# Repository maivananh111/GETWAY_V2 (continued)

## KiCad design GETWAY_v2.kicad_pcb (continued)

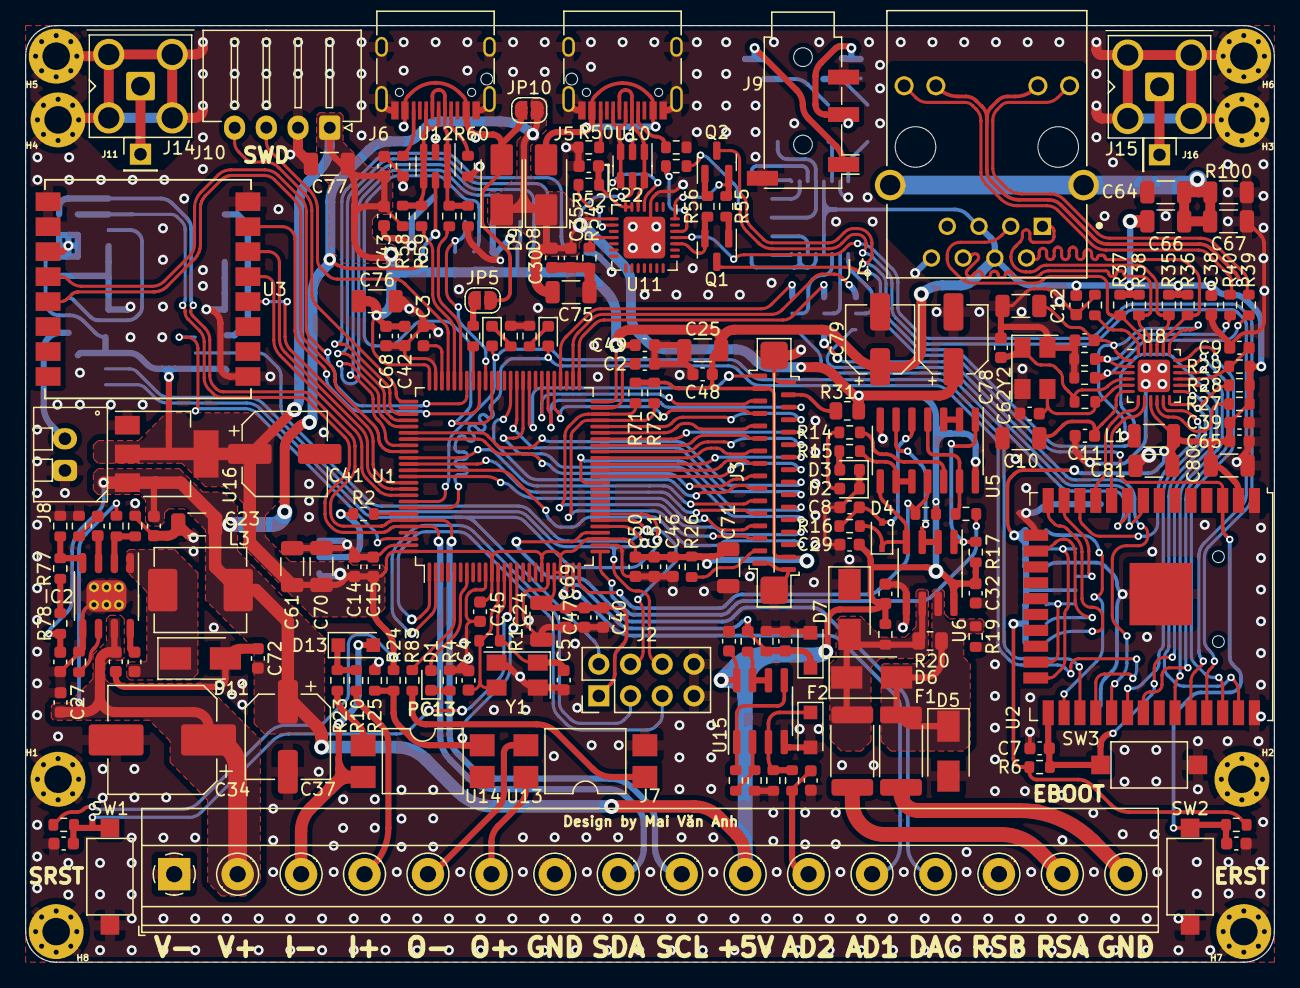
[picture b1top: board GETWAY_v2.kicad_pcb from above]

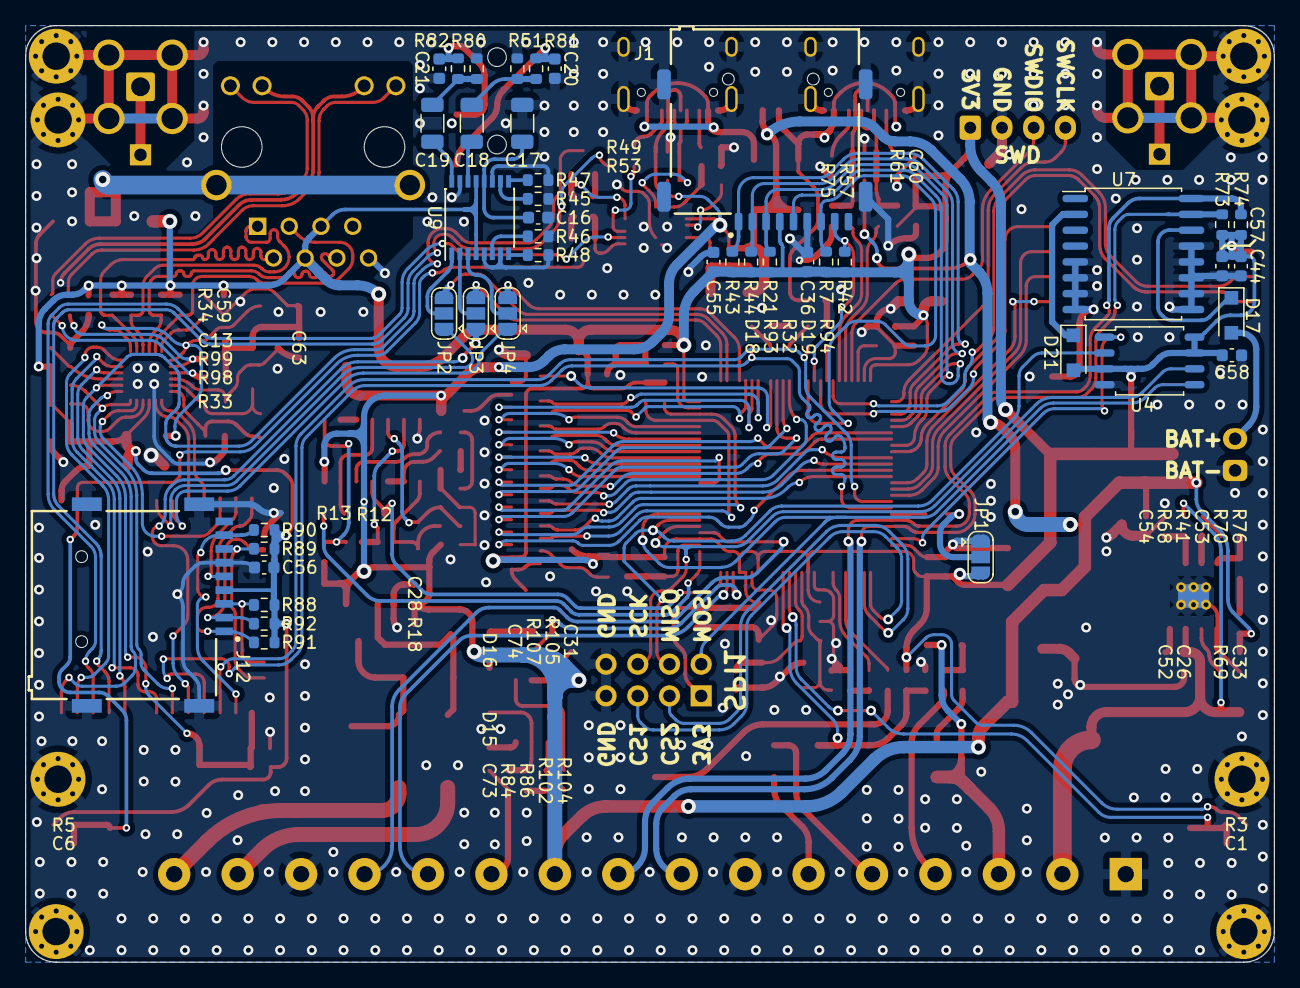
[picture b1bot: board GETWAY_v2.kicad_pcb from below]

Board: 2 copper layers, 100.0 x 75.0 mm, 242 parts (43 on the bottom side), 188 nets.
